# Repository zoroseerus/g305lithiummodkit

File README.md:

# g305lithiummodkit
a modkit for the Logitech G305 so you can use lithium batteries and save some weight

Hi there,

Some time ago, enncoo sort of dropped off and nobody is sure what happened to them. As such there's been a hole that their modkit served, so I paid somebody to reverse engineer it on fiverr (@duca99, https://www.fiverr.com/duca99?source=gig_page) so this could be remedied. It seems right to release the files since it's not my design. Hopefully this helps someone.

If you're just interested in buying the modkits, I'll be selling those on https://www.etsy.com/listing/1679779226/logitech-g305-modkit-for-weight , but you can also take these files to a site to make them *queue PCBWAY sponsor segment of the video... wait this isn't YouTube. I digress*. 

I'm uploading the files on here as I was given them, as I'm pretty unfamiliar with PCB design and github such. If there's a signiciantly better way to group them or such feel free to let me know and I can re-arrange things as needed.

I'm under the impression that any (correctly pinned) 3.7V lithium ion batteries should work with it. my example photos are with a 150mAh one as it's a decent size while not being particularly massive, but you can go smaller or larger as desired I believe.

simplified diagram of how it's hooked up:

used in a mice:

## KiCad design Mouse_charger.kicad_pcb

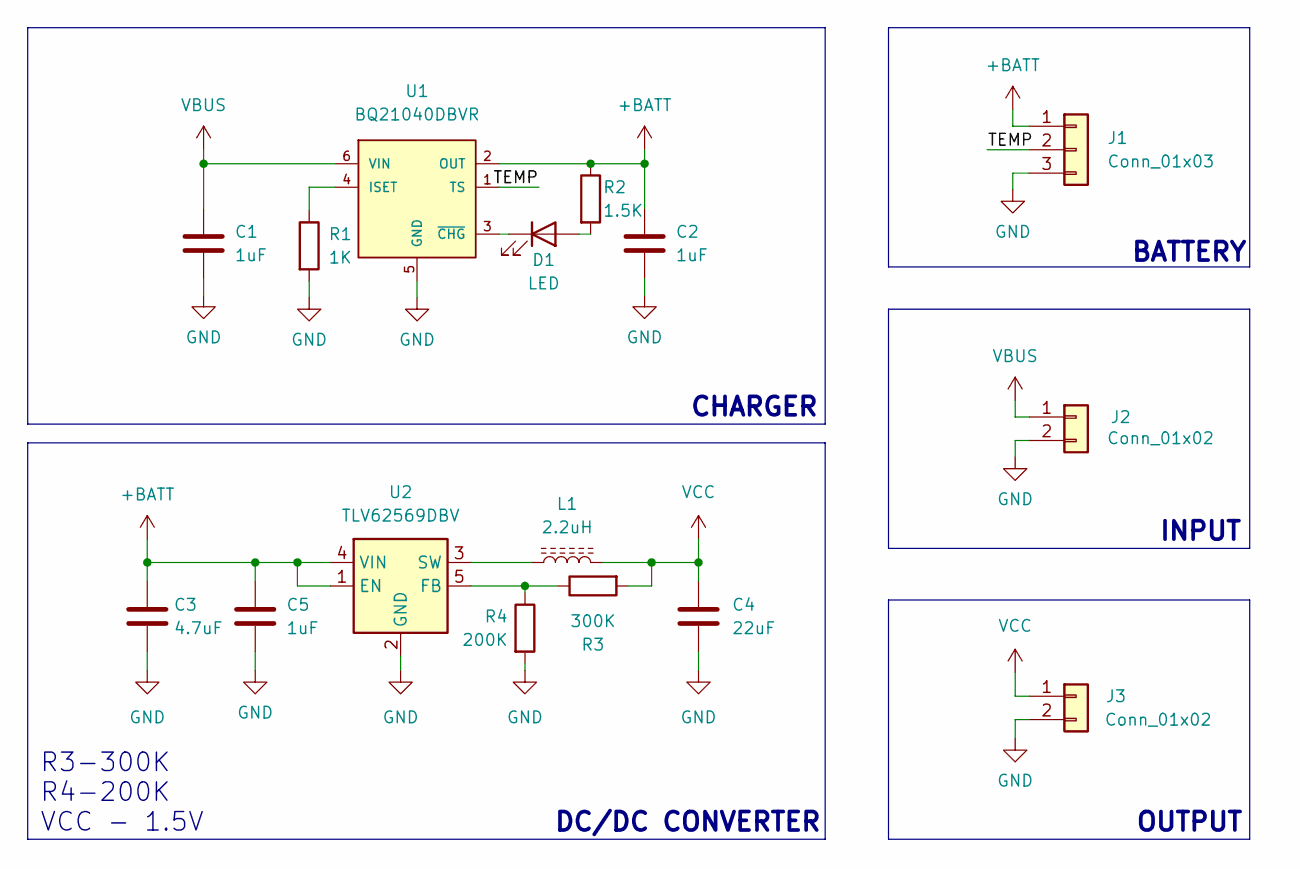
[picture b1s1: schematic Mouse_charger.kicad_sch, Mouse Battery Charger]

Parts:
C1, C2, C5: 1uF; C_0402_1005Metric
C3: 4.7uF; C_0603_1608Metric
C4: 22uF; C_0603_1608Metric
D1: LED; LED_0402_1005Metric
J1: Conn_01x03; JST_SH_BM03B-SRSS-TB_1x03-1MP_P1.00mm_Vertical
J2, J3: Conn_01x02; JST_SH_BM02B-SRSS-TB_1x02-1MP_P1.00mm_Vertical
L1: 2.2uH; INDP4040X180N
R1: 1K; R_0402_1005Metric
R2: 1.5K; R_0402_1005Metric
R3: 300K; R_0402_1005Metric
R4: 200K; R_0402_1005Metric
U1: BQ21040DBVR; SOT95P280X145-6N
U2: TLV62569DBV; SOT-23-5

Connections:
+BATT: C2.1, C3.1, C5.1, J1.1, R2.1, U1.2 (OUT), U2.1 (EN), U2.4 (VIN)
/TEMP: J1.2, U1.1 (TS)
GND: C1.2, C2.2, C3.2, C4.2, C5.2, J1.3, J2.2, J3.2, R1.2, R4.2, U1.5 (GND), U2.2 (GND)
unnamed: D1.2 (A), R2.2
unnamed: D1.1 (K), U1.3 (~CHG)
unnamed: R1.1, U1.4 (ISET)
unnamed: R3.1, R4.1, U2.5 (FB)
unnamed: L1.1, U2.3 (SW)
VBUS: C1.1, J2.1, U1.6 (VIN)
VCC: C4.1, J3.1, L1.2, R3.2

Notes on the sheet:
BATTERY
R3-300K R4-200K VCC - 1.5V
OUTPUT
DC/DC CONVERTER
INPUT
CHARGER

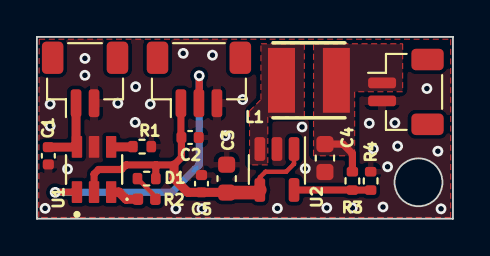
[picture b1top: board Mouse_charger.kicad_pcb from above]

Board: 2 copper layers, 23.1 x 10.1 mm, 16 parts (0 on the bottom side), 10 nets.

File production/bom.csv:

Designator,Footprint,Quantity,Value,LCSC Part #
"C1, C2, C5",402,3,1uF,C326568
C3,603,1,4.7uF,C277476
C4,603,1,22uF,C109447
D1,402,1,LED,C434449
J1,JST_SH_BM03B-SRSS-TB_1x03-1MP_P1.00mm_Vertical,1,Conn_01x03,C160389
"J2, J3",JST_SH_BM02B-SRSS-TB_1x02-1MP_P1.00mm_Vertical,2,Conn_01x02,C160388
L1,INDP4040X180N,1,2.2uH,C167825
R1,402,1,1K,C106235
R2,402,1,1.5K,C105872
R3,402,1,300K,C138011
R4,402,1,200K,C114763
U1,SOT95P280X145-6N,1,BQ21040DBVR,C202311
U2,SOT-23-5,1,TLV62569DBV,C141836

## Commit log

2024-03-09 Create placeholder
2024-03-09 Create pl
2024-03-09 Create asd
2024-03-09 Create pla
2024-03-26 Create JLPCB instructions
2024-03-26 Update JLPCB instructions
2026-04-13 Create notion page with research and other links I used
